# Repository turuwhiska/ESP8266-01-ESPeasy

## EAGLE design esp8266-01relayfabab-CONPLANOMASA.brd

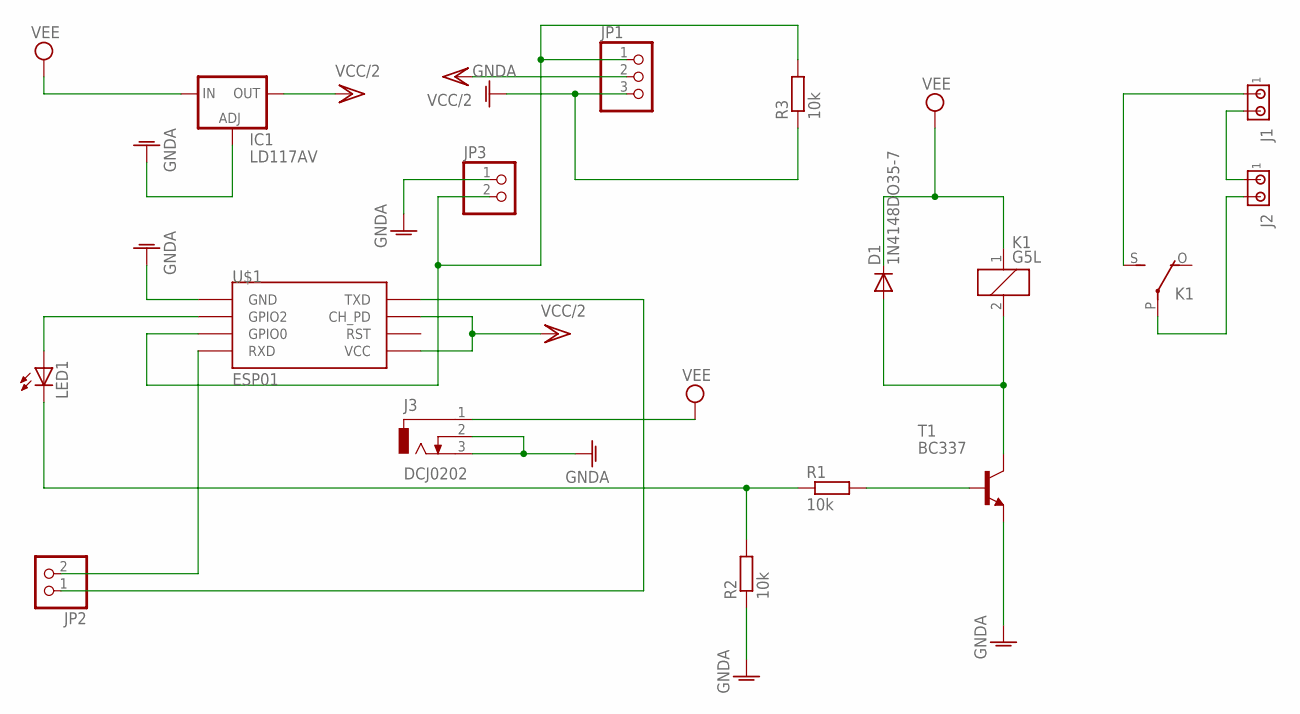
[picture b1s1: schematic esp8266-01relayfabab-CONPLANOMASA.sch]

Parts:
D1: 1N4148DO35-7; DO35-7
IC1: LD117AV; TO220L1
J1, J2: MTA02-156; 1X2MTA
J3: DCJ0202
JP1: PINHD-1X3; 1X03
JP2, JP3: PINHD-1X2; 1X02
K1: G5L; G5LE
LED1: LED5MM
R1, R2, R3: 10k; 0207/7
T1: BC337; TO92
U$1: ESP01

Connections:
GND: IC1.1 (ADJ), J3.2, J3.3, JP1.3, JP3.1, R2.1, R3.1, T1.1 (E), U$1.GND
unnamed: J1.2, J2.1
unnamed: LED1.K (C), R1.1, R2.2
unnamed: JP1.1, JP3.2, R3.2, U$1.GPIO0
unnamed: JP2.1, U$1.TX (TXD)
unnamed: JP2.2, U$1.RX (RXD)
unnamed: D1.A, K1.2, T1.3 (C)
unnamed: R1.2, T1.2 (B)
unnamed: J1.1, K1.S
unnamed: J2.2, K1.P
unnamed: LED1.A, U$1.GPIO2
VCC/2: IC1.2 (OUT), JP1.2, U$1.CH_PD, U$1.VCC
VEE: D1.C, IC1.3 (IN), J3.1, K1.1

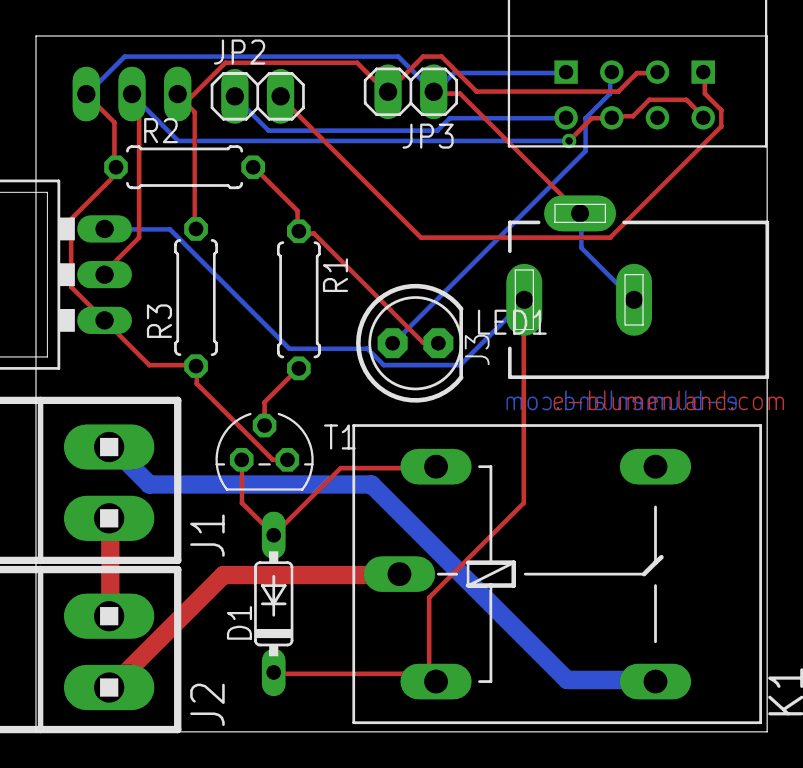
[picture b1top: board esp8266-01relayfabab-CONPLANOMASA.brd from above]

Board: 2 copper layers, 40.6 x 38.7 mm, 15 parts (1 on the bottom side), 13 nets.
